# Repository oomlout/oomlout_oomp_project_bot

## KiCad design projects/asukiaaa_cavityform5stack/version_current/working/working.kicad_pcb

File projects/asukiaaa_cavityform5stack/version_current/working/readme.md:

# OOMP Project  
## CavityForM5Stack  by asukiaaa  
  
oomp key: oomp_projects_flat_asukiaaa_cavityform5stack  
(snippet of original readme)  
  
- CavityForM5Stack  
  
PCBs to create a cavity for M5Stack.  

- License  
  
MIT  
  
- References  
  
- [CavityForM5Stack ピンソケット、ブレッドボード無し](https://www.switch-science.com/catalog/5684/)  
- [CavityForM5Stack ピンソケット、ブレッドボード付き](https://www.switch-science.com/catalog/5685/)  
- [M5StackのStackに背の高い部品を利用できるM5StackCavityを作ってみた](http://asukiaaa.blogspot.com/2019/08/m5stackstackm5stackcavity.html)  
  
  full source readme at [readme_src.md](readme_src.md)  
  
source repo at: [https://github.com/asukiaaa/CavityForM5Stack](https://github.com/asukiaaa/CavityForM5Stack)  
## Board  

## Schematic  

[schematic pdf](working_schematic.pdf)  
## Images

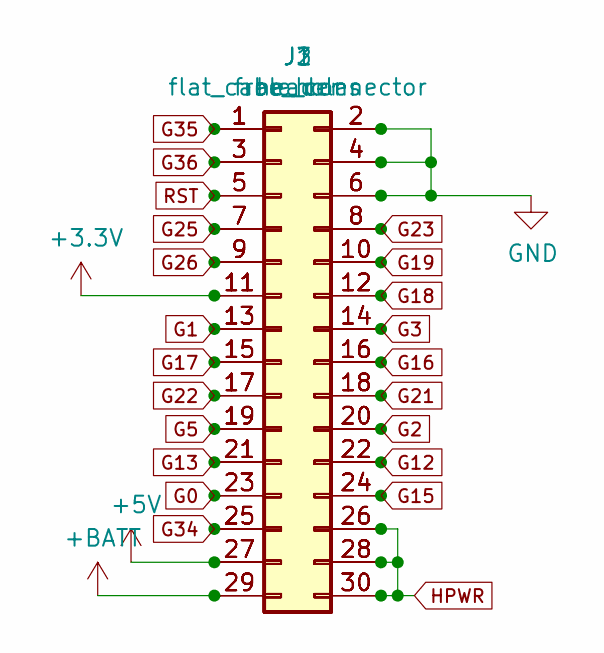
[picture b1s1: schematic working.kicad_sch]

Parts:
J1: flat_cable_connector; Hirose_FH12-30S-0.5SH_1x30-1MP_P0.50mm_Horizontal
J2: header; PinHeader_2x15_P2.54mm_Vertical_SMD_for_M5Stack
J3: free_holes; PinHeader_1x30_P1.27mm_Vertical_without_silks

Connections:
+3V3: J1.11, J2.11, J3.11
+5V: J1.27, J2.27, J3.27
+BATT: J1.29, J2.29, J3.29
G0: J1.23, J2.23, J3.23
G1: J1.13, J2.13, J3.13
G2: J1.20, J2.20, J3.20
G3: J1.14, J2.14, J3.14
G5: J1.19, J2.19, J3.19
G12: J1.22, J2.22, J3.22
G13: J1.21, J2.21, J3.21
G15: J1.24, J2.24, J3.24
G16: J1.16, J2.16, J3.16
G17: J1.15, J2.15, J3.15
G18: J1.12, J2.12, J3.12
G19: J1.10, J2.10, J3.10
G21: J1.18, J2.18, J3.18
G22: J1.17, J2.17, J3.17
G23: J1.8, J2.8, J3.8
G25: J1.7, J2.7, J3.7
G26: J1.9, J2.9, J3.9
G34: J1.25, J2.25, J3.25
G35: J1.1, J2.1, J3.1
G36: J1.3, J2.3, J3.3
GND: J1.2, J1.4, J1.6, J2.2, J2.4, J2.6, J3.2, J3.4, J3.6
HPWR: J1.26, J1.28, J1.30, J2.26, J2.28, J2.30, J3.26, J3.28, J3.30
RST: J1.5, J2.5, J3.5

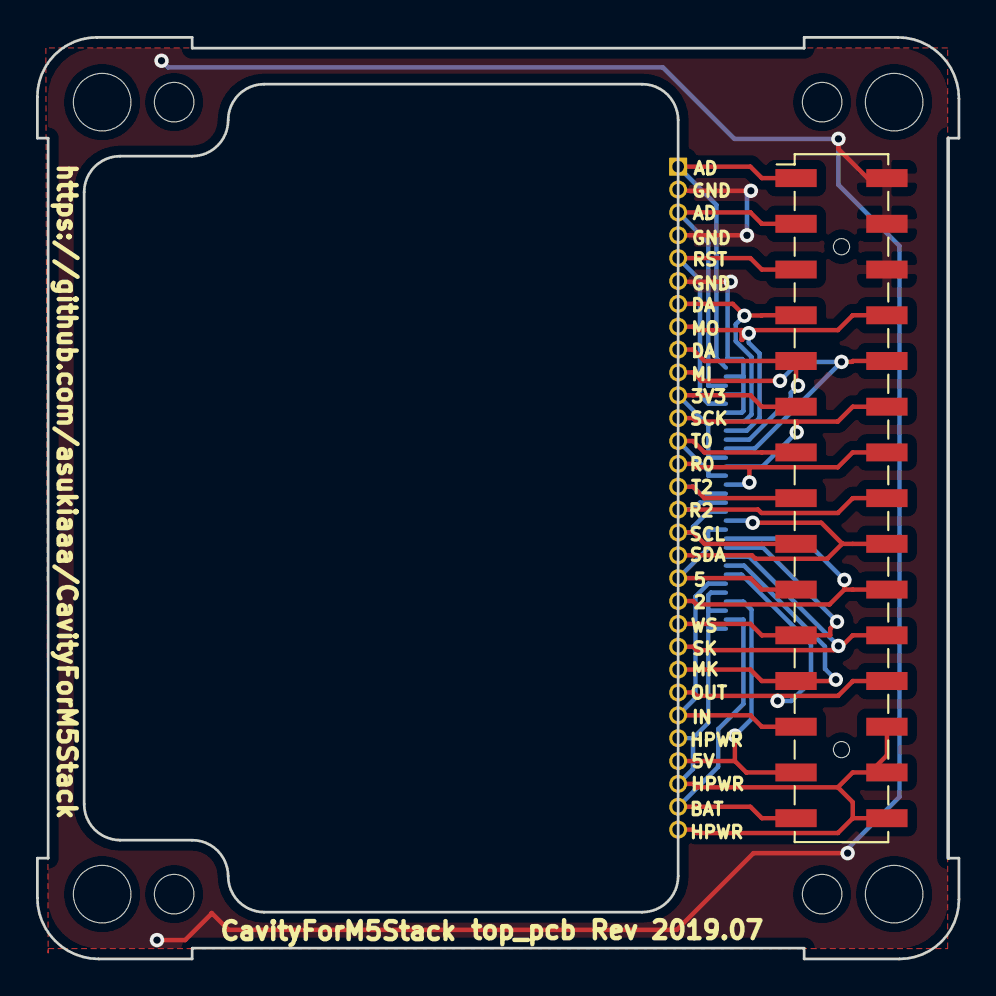
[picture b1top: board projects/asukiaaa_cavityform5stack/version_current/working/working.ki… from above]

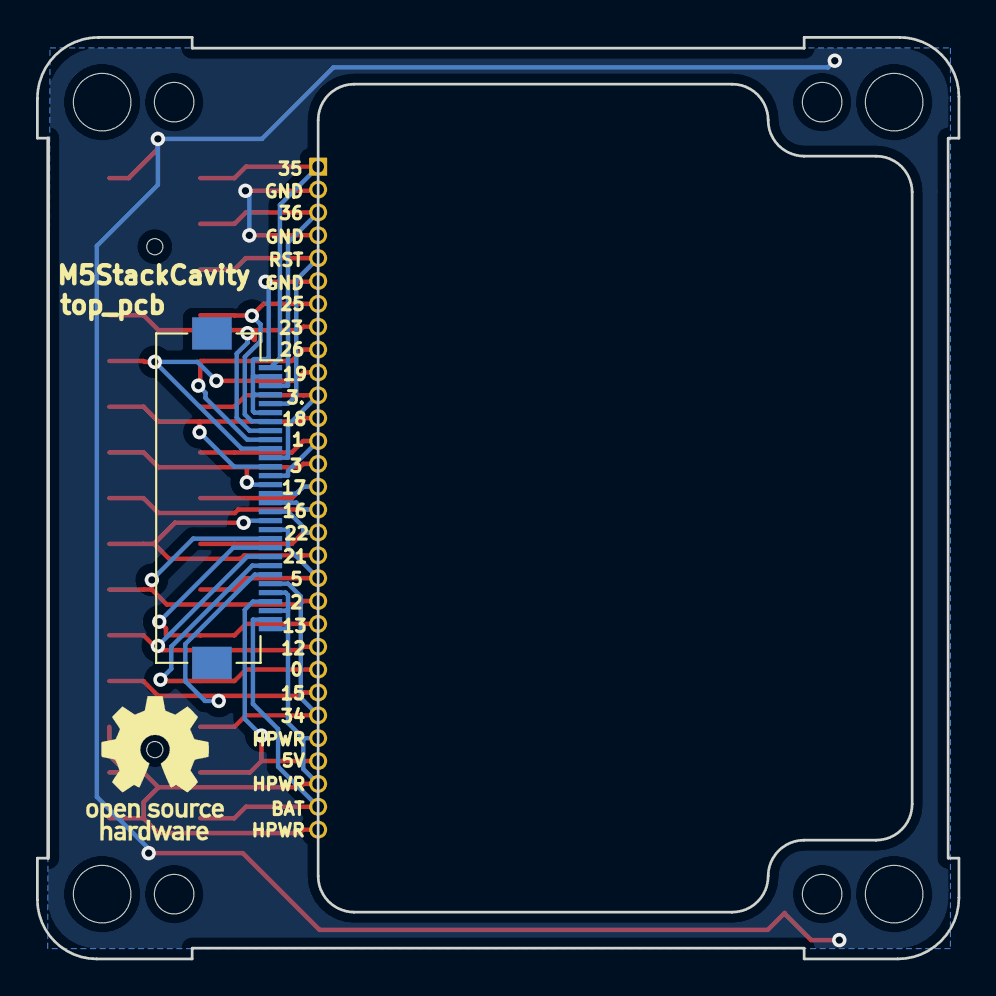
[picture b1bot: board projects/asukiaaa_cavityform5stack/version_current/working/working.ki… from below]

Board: 2 copper layers, 51.2 x 51.2 mm, 16 parts (2 on the bottom side), 26 nets.

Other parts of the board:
OSHWREF2: OSHW-Logo_7.5x8mm_SilkScreen
REF1, REF4, REF6, REF9: MountingHole_3.2mm_M3
REF2, REF3, REF7, REF8: MountingHole_2.2mm_M2
corner1, corner4: corner_edge1
corner2, corner3: corner_edge2

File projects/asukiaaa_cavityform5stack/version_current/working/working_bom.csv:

"Id";"Designator";"Footprint";"Quantity";"Designation";"Supplier and ref";
1;"J2";"PinHeader_2x15_P2.54mm_Vertical_SMD_for_M5Stack";1;"header";;;
2;"corner4,corner1";"corner_edge1";2;"corner_edge1";;;
3;"corner3,corner2";"corner_edge2";2;"corner_edge2";;;
4;"J1";"Hirose_FH12-30S-0.5SH_1x30-1MP_P0.50mm_Horizontal";1;"flat_cable_connector";;;
5;"J3";"PinHeader_1x30_P1.27mm_Vertical_without_silks";1;"free_holes";;;

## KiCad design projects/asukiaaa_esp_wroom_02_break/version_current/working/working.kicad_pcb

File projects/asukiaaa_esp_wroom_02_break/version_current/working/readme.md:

# esp-wroom-02-break by asukiaaa  
This is a harvested standardized copy of a project from github.  
The original project can be found at:  
https://github.com/asukiaaa/esp-wroom-02-break  
Please consult that link for additional, details, files, and license information.  
Note: It was auto harvested and if the original repo had more than one board file or anything out of the ordinary the files here are likely not representative.

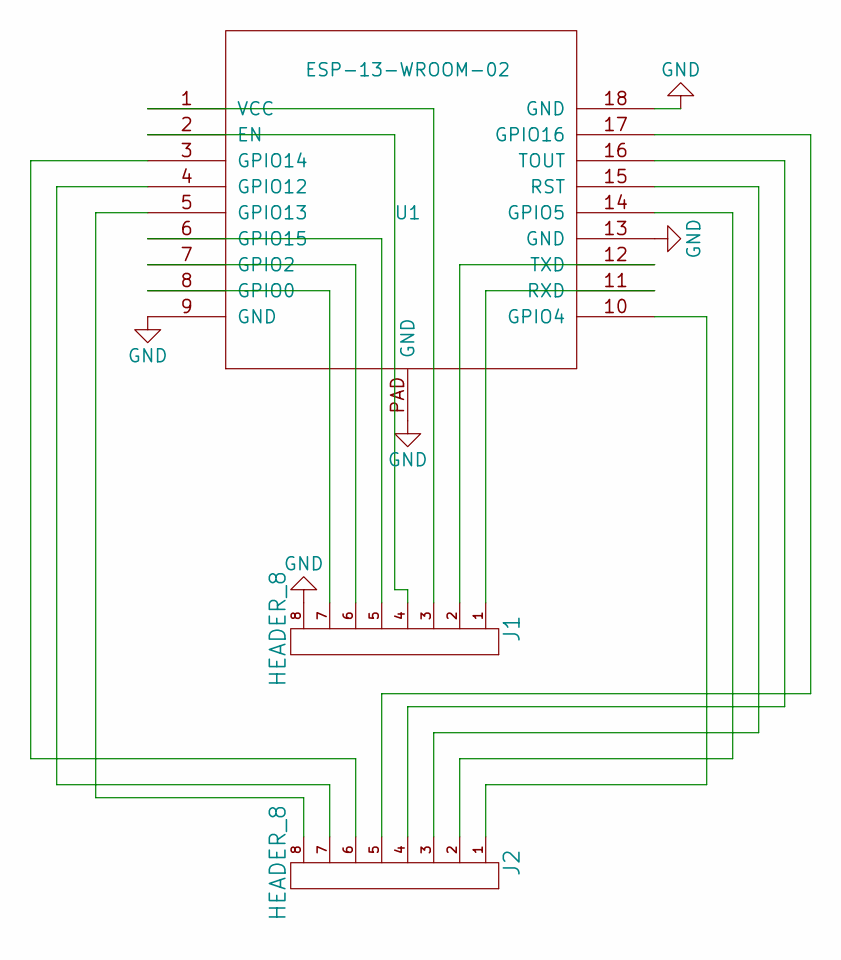
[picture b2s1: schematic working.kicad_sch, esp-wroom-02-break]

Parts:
J1, J2: HEADER_8; Pin_Header_Straight_1x08_small
U1: ESP-13-WROOM-02

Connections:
GND: J1.8, U1.9 (GND), U1.13 (GND), U1.18 (GND), U1.PAD (GND)
unnamed: J1.1, U1.11 (RXD)
unnamed: J1.2, U1.12 (TXD)
unnamed: J1.3, U1.1 (VCC)
unnamed: J1.4, U1.2 (EN)
unnamed: J1.5, U1.6 (GPIO15)
unnamed: J1.6, U1.7 (GPIO2)
unnamed: J1.7, U1.8 (GPIO0)
unnamed: J2.1, U1.10 (GPIO4)
unnamed: J2.2, U1.14 (GPIO5)
unnamed: J2.3, U1.15 (RST)
unnamed: J2.4, U1.16 (TOUT)
unnamed: J2.5, U1.17 (GPIO16)
unnamed: J2.6, U1.3 (GPIO14)
unnamed: J2.7, U1.4 (GPIO12)
unnamed: J2.8, U1.5 (GPIO13)

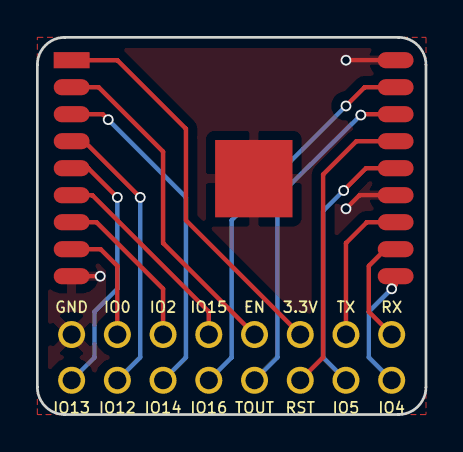
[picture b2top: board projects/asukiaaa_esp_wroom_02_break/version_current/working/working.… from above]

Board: 2 copper layers, 21.6 x 21.0 mm, 3 parts (0 on the bottom side), 16 nets.

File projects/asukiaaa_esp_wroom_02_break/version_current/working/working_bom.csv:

"Id";"Designator";"Footprint";"Quantity";"Designation";"Supplier and ref";
1;"U1";"ESP-13-WROOM-02";1;"ESP-13-WROOM-02";;;
2;"J1,J2";"Pin_Header_Straight_1x08_small";2;"HEADER_8";;;
3;"G***";"oshw-3p4mm";1;"LOGO";;;

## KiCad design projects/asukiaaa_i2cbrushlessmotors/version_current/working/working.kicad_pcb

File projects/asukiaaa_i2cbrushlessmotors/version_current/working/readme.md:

# I2cBrushlessMotors by asukiaaa  
This is a harvested standardized copy of a project from github.  
The original project can be found at:  
https://github.com/asukiaaa/I2cBrushlessMotors  
Please consult that link for additional, details, files, and license information.  
Note: It was auto harvested and if the original repo had more than one board file or anything out of the ordinary the files here are likely not representative.

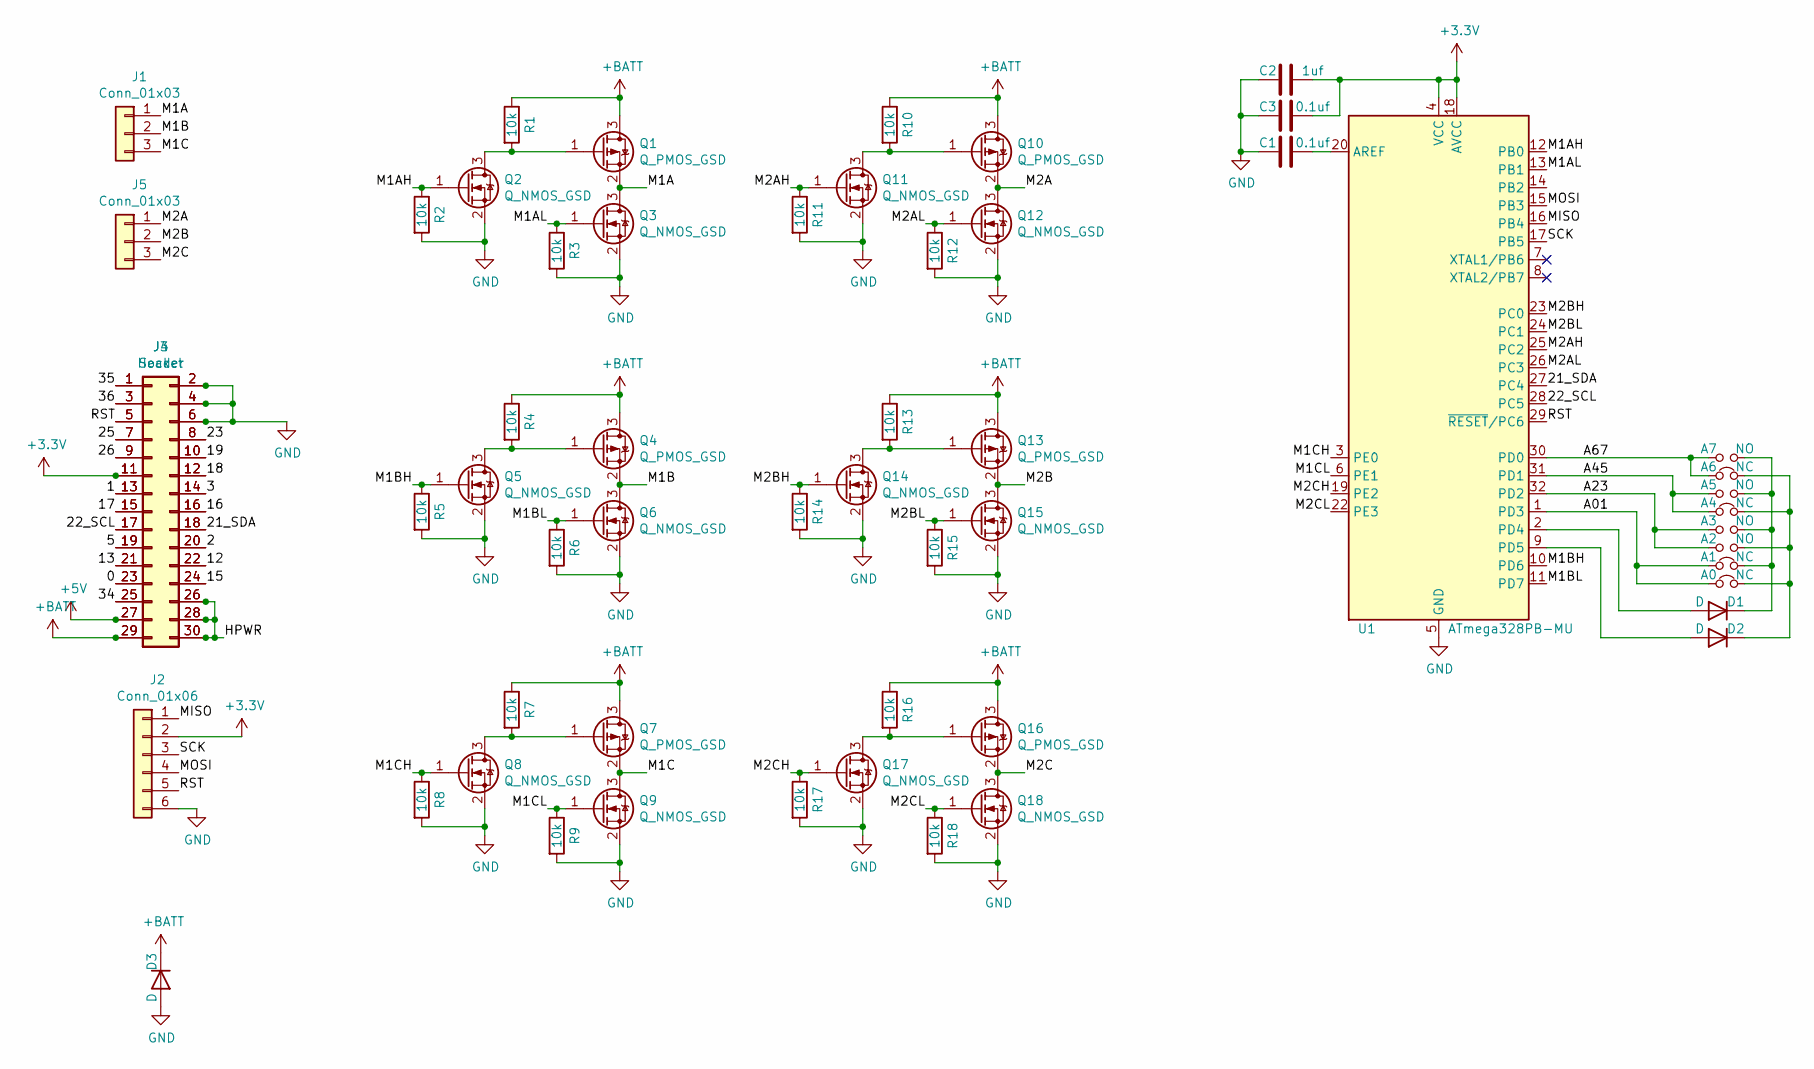
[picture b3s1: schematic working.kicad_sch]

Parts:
A0, A1, A4, A6: NC; SolderJumper-2_P1.3mm_Bridged_RoundedPad1.0x1.5mm
A2, A3, A5, A7: NO; SolderJumper-2_P1.3mm_Open_RoundedPad1.0x1.5mm
C1, C3: 0.1uf; C_0603_1608Metric
C2: 1uf; C_0603_1608Metric
D1, D2: D; D_SOD-323
D3: D; D_SOD-123F
J1, J5: Conn_01x03; Molex_1x03_P1.25mm_Vertical
J2: Conn_01x06; 2x03_P2.54mm_Pads
J3: Header; PinHeader_2x15_P2.54mm_M5Stack
J4: Socket; PinSocket_2x15_P2.54mm_Vertical_SMD_just_for_M5Stack_bottom
Q1, Q4, Q7, Q10, Q13, Q16: Q_PMOS_GSD; SOT-23
Q2, Q3, Q5, Q6, Q8, Q9, Q11, Q12, Q14, Q15, Q17, Q18: Q_NMOS_GSD; SOT-23
R1, R2, R3, R4, R5, R6, R7, R8, R9, R10, R11, R12, R13, R14, R15, R16, R17, R18: 10k; R_0603_1608Metric
U1: ATmega328PB-MU; QFN-32-1EP_5x5mm_P0.5mm_EP3.1x3.1mm

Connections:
+3V3: C2.2, C3.2, J2.2, J3.11, J4.11, U1.4 (VCC), U1.18 (AVCC)
+5V: J3.27, J4.27
+BATT: D3.1 (K), J3.29, J4.29, Q1.3 (D), Q4.3 (D), Q7.3 (D), Q10.3 (D), Q13.3 (D), Q16.3 (D), R1.1, R4.1, R7.1, R10.1, R13.1, R16.1
/0: J3.23, J4.23
/1: J3.13, J4.13
/2: J3.20, J4.20
/3: J3.14, J4.14
/5: J3.19, J4.19
/12: J3.22, J4.22
/13: J3.21, J4.21
/15: J3.24, J4.24
/16: J3.16, J4.16
/17: J3.15, J4.15
/18: J3.12, J4.12
/19: J3.10, J4.10
/21_SDA: J3.18, J4.18, U1.27 (PC4)
/22_SCL: J3.17, J4.17, U1.28 (PC5)
/23: J3.8, J4.8
/25: J3.7, J4.7
/26: J3.9, J4.9
/34: J3.25, J4.25
/35: J3.1, J4.1
/36: J3.3, J4.3
/A01: A0.1, A1.1, U1.1 (PD3)
/A23: A2.1, A3.1, U1.32 (PD2)
/A45: A4.1, A5.1, U1.31 (PD1)
/A67: A6.1, A7.1, U1.30 (PD0)
/HPWR: J3.26, J3.28, J3.30, J4.26, J4.28, J4.30
/M1A: J1.1, Q1.2 (S), Q3.3 (D)
/M1AH: Q2.1 (G), R2.1, U1.12 (PB0)
/M1AL: Q3.1 (G), R3.1, U1.13 (PB1)
/M1B: J1.2, Q4.2 (S), Q6.3 (D)
/M1BH: Q5.1 (G), R5.1, U1.10 (PD6)
/M1BL: Q6.1 (G), R6.1, U1.11 (PD7)
/M1C: J1.3, Q7.2 (S), Q9.3 (D)
/M1CH: Q8.1 (G), R8.1, U1.3 (PE0)
/M1CL: Q9.1 (G), R9.1, U1.6 (PE1)
/M2A: J5.1, Q10.2 (S), Q12.3 (D)
/M2AH: Q11.1 (G), R11.1, U1.25 (PC2)
/M2AL: Q12.1 (G), R12.1, U1.26 (PC3)
/M2B: J5.2, Q13.2 (S), Q15.3 (D)
/M2BH: Q14.1 (G), R14.1, U1.23 (PC0)
/M2BL: Q15.1 (G), R15.1, U1.24 (PC1)
/M2C: J5.3, Q16.2 (S), Q18.3 (D)
/M2CH: Q17.1 (G), R17.1, U1.19 (PE2)
/M2CL: Q18.1 (G), R18.1, U1.22 (PE3)
/MISO: J2.1, U1.16 (PB4)
/MOSI: J2.4, U1.15 (PB3)
/RST: J2.5, J3.5, J4.5, U1.29 (~RESET/PC6)
/SCK: J2.3, U1.17 (PB5)
GND: C1.1, C2.1, C3.1, D3.2 (A), J2.6, J3.2, J3.4, J3.6, J4.2, J4.4, J4.6, Q2.2 (S), Q3.2 (S), Q5.2 (S), Q6.2 (S), Q8.2 (S), Q9.2 (S), Q11.2 (S), Q12.2 (S), Q14.2 (S), Q15.2 (S), Q17.2 (S), Q18.2 (S), R2.2, R3.2, R5.2, R6.2, R8.2, R9.2, R11.2, R12.2, R14.2, R15.2, R17.2, R18.2, U1.5 (GND), U1.21 (GND), U1.33 (GND)
unnamed: A0.2, A2.2, A4.2, A6.2, D2.1 (K)
unnamed: A1.2, A3.2, A5.2, A7.2, D1.1 (K)
unnamed: C1.2, U1.20 (AREF)
unnamed: D1.2 (A), U1.2 (PD4)
unnamed: D2.2 (A), U1.9 (PD5)
unnamed: Q1.1 (G), Q2.3 (D), R1.2
unnamed: Q4.1 (G), Q5.3 (D), R4.2
unnamed: Q7.1 (G), Q8.3 (D), R7.2
unnamed: Q10.1 (G), Q11.3 (D), R10.2
unnamed: Q13.1 (G), Q14.3 (D), R13.2
unnamed: Q16.1 (G), Q17.3 (D), R16.2

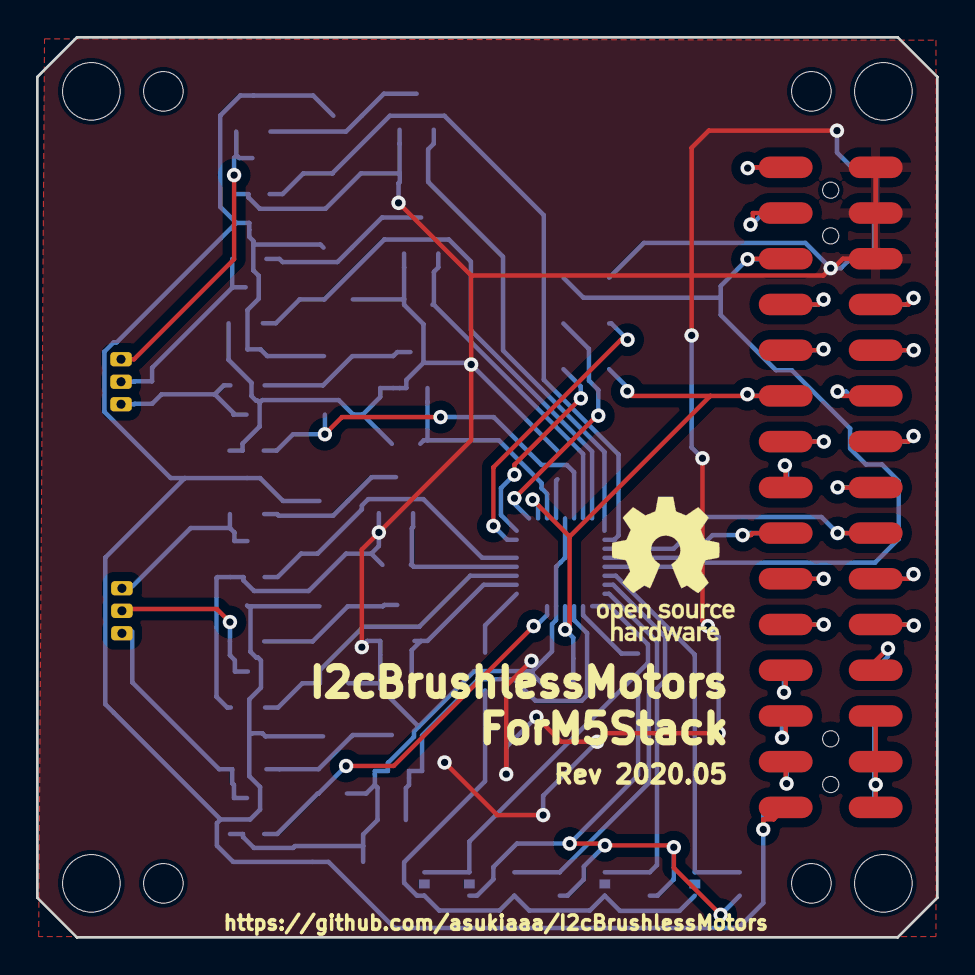
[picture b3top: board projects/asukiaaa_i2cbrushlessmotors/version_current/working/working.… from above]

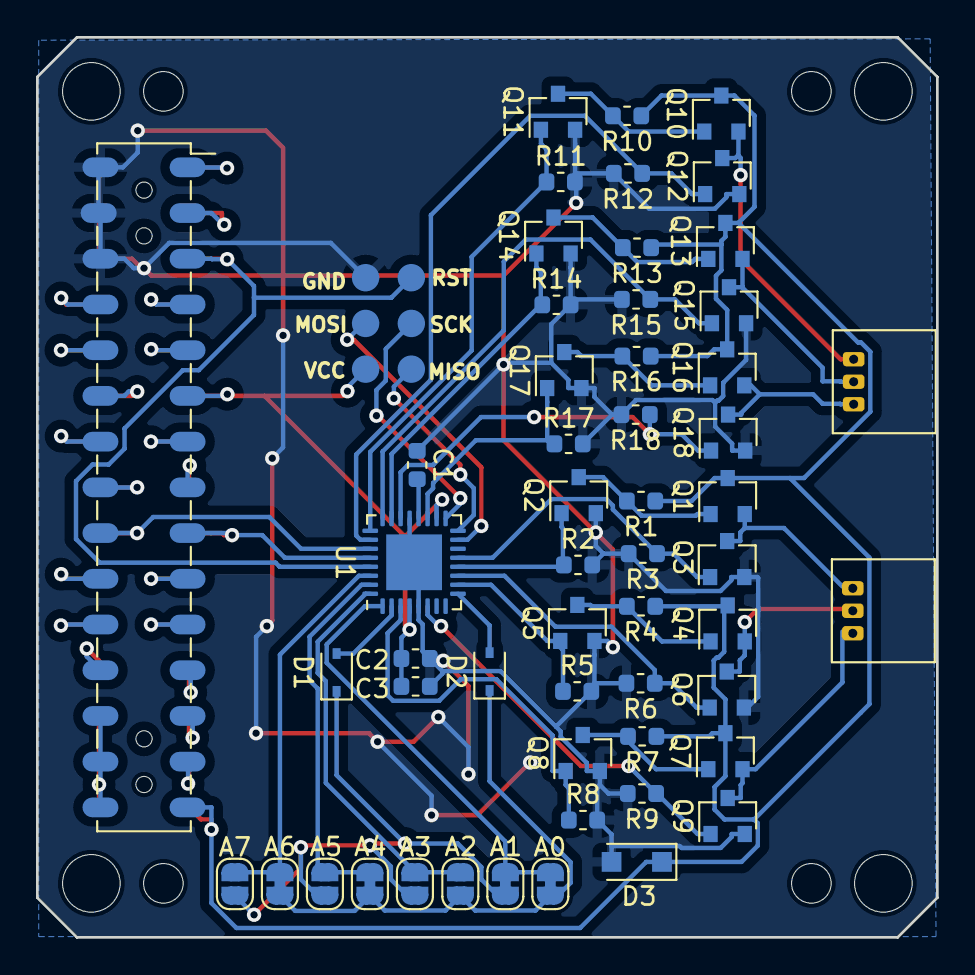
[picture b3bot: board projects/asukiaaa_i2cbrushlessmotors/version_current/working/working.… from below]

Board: 2 copper layers, 50.0 x 50.0 mm, 64 parts (55 on the bottom side), 62 nets.

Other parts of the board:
REF1, REF4, REF6, REF9: MountingHole_3.2mm_M3
REF2, REF3, REF7, REF8: MountingHole_2.2mm_M2

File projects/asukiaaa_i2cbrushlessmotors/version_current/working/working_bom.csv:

"Id";"Designator";"Footprint";"Quantity";"Designation";"Supplier and ref";
1;"J5,J1";"Molex_1x03_P1.25mm_Vertical";2;"Conn_01x03";;;
2;"D2,D1";"D_SOD-323";2;"D";;;
3;"D3";"D_SOD-123F";1;"D";;;
4;"C3,C1";"C_0603_1608Metric";2;"0.1uf";;;
5;"C2";"C_0603_1608Metric";1;"1uf";;;
6;"R9,R8,R2,R1,R4,R10,R12,R15,R5,R7,R16,R14,R11,R18,R6,R13,R17,R3";"R_0603_1608Metric";18;"10k";;;
7;"Q7,Q1,Q4,Q10,Q13,Q16";"SOT-23";6;"Q_PMOS_GSD";;;
8;"Q15,Q18,Q6,Q14,Q9,Q5,Q12,Q8,Q3,Q17,Q11,Q2";"SOT-23";12;"Q_NMOS_GSD";;;
9;"U1";"QFN-32-1EP_5x5mm_P0.5mm_EP3.1x3.1mm";1;"ATmega328PB-MU";;;
10;"J3";"PinHeader_2x15_P2.54mm_M5Stack";1;"Header";;;
11;"J2";"2x03_P2.54mm_Pads";1;"Conn_01x06";;;
12;"J4";"PinSocket_2x15_P2.54mm_Vertical_SMD_just_for_M5Stack_bottom";1;"Socket";;;

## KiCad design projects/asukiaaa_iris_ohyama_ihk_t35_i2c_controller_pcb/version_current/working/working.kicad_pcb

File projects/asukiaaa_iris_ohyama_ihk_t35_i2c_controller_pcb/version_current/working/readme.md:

# IRIS-OHYAMA-IHK-T35-I2C-Controller-PCB by asukiaaa  
This is a harvested standardized copy of a project from github.  
The original project can be found at:  
https://github.com/asukiaaa/IRIS-OHYAMA-IHK-T35-I2C-Controller-PCB  
Please consult that link for additional, details, files, and license information.  
Note: It was auto harvested and if the original repo had more than one board file or anything out of the ordinary the files here are likely not representative.

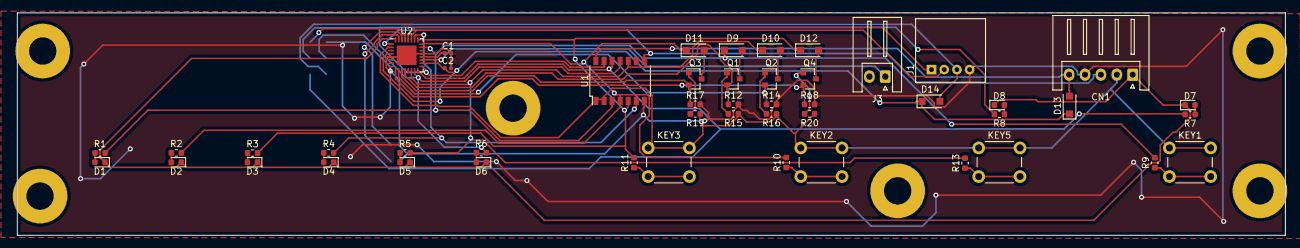
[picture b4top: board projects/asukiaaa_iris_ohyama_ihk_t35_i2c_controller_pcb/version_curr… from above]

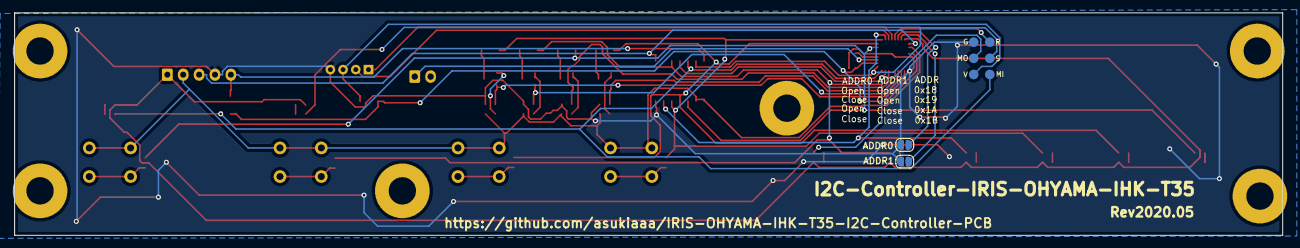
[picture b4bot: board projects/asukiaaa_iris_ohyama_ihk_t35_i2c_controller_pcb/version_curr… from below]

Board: 2 copper layers, 199.5 x 35.0 mm, 58 parts (3 on the bottom side), 46 nets.

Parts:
C1, C2: 0.1uf; C_0402_1005Metric
CN1: Conn_01x05; JST_XH_S5B-XH-A_1x05_P2.50mm_Horizontal
D1: Level1; LED_0603_1608Metric
D2: Level2; LED_0603_1608Metric
D3: Level3; LED_0603_1608Metric
D4: Level4; LED_0603_1608Metric
D5: Level5; LED_0603_1608Metric
D6: Level6; LED_0603_1608Metric
D7: NomalState; LED_0603_1608Metric
D8: OilState; LED_0603_1608Metric
D9, D10, D11, D12, D13, D14: D; D_SOD-123F
J1: Grove; NS-Tech_Grove_1x04_P2mm_Horizontal
J2: Conn_01x06; 2x03_P2.54mm_Pads
J3: thermistor; JST_XH_S2B-XH-A_1x02_P2.50mm_Horizontal
JP1: ADDR0_NO; SolderJumper-2_P1.3mm_Open_RoundedPad1.0x1.5mm
JP2: ADDR1_NO; SolderJumper-2_P1.3mm_Open_RoundedPad1.0x1.5mm
KEY1: normal_power; SW_PUSH_6mm_center_like_smd
KEY2: power_up; SW_PUSH_6mm_center_like_smd
KEY3: power_down; SW_PUSH_6mm_center_like_smd
KEY5: oil_power; SW_PUSH_6mm_center_like_smd
Q1, Q2, Q3, Q4: Q_NMOS_DGS; SOT-23
R1, R2, R3, R4, R5, R6, R7, R8, R12, R14, R15, R16, R17, R18, R19, R20: 1k; R_0603_1608Metric
R9, R10, R11, R13: 2k; R_0603_1608Metric
REF1, REF2, REF3, REF4, REF5, REF6: MountingHole_4.3mm_M4_Pad
U1: 74HC164; SOP-14_4.4x9.2mm_P1.27mm
U2: ATmega328P-MU; QFN-32-1EP_5x5mm_P0.5mm_EP3.1x3.1mm

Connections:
+5V: CN1.5, D13.2, U1.14
/A0: D9.1, R1.2, R9.2, U1.3, U2.23
/A1: D11.1, R2.2, R10.2, U1.4, U2.24
/A2: D12.1, R3.2, R11.2, U1.5, U2.25
/A3: R4.2, U1.6, U2.26
/A6: J3.1, U2.19
/ADDR0: JP1.1, U2.30
/ADDR1: JP2.1, U2.31
/CLK: CN1.3, U1.8, U2.1
/Controller_5V: C2.1, D13.1, D14.1, U2.4, U2.18
/D2: CN1.1, D1.1, D2.1, D3.1, D4.1, D5.1, D6.1, D7.1, D8.1, U2.32
/D4: CN1.2, KEY1.1, KEY2.1, KEY3.1, KEY5.1, R15.1, R16.1, R19.1, R20.1, U1.1, U1.2, U2.2
/D5: Q4.2, R18.1, U2.9
/D6: Q2.2, R14.1, U2.10
/D7: Q3.2, R17.1, U2.11
/D8: Q1.2, R12.1, U2.12
/D10: D10.1, R5.2, R13.2, U1.10, U2.14
/D11: J2.4, R6.2, U1.11, U2.15
/D12: J2.1, R7.2, U1.12, U2.16
/D13: J2.3, R8.2, U1.13, U2.17
/GROVE_5V: D14.2, J1.3, J2.2
/RST: J2.5, U2.29
/SCL: J1.1, U2.28
/SDA: J1.2, U2.27
GND: C1.2, C2.2, CN1.4, J1.4, J2.6, JP1.2, JP2.2, R12.2, R14.2, R17.2, R18.2, U1.7, U2.5, U2.21, U2.33
unnamed: C1.1, U2.20
unnamed: D1.2, R1.1
unnamed: D2.2, R2.1
unnamed: D3.2, R3.1
unnamed: D4.2, R4.1
unnamed: D5.2, R5.1
unnamed: D6.2, R6.1
unnamed: D7.2, R7.1
unnamed: D8.2, R8.1
unnamed: D9.2, Q1.3
unnamed: D10.2, Q2.3
unnamed: D11.2, Q3.3
unnamed: D12.2, Q4.3
unnamed: KEY1.2, R9.1
unnamed: KEY2.2, R10.1
unnamed: KEY3.2, R11.1
unnamed: KEY5.2, R13.1
unnamed: Q1.1, R15.2
unnamed: Q2.1, R16.2
unnamed: Q3.1, R19.2
unnamed: Q4.1, R20.2

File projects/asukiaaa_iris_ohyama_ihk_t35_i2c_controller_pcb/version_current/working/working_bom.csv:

"Id";"Designator";"Footprint";"Quantity";"Designation";"Supplier and ref";
1;"KEY5";"SW_PUSH_6mm_center_like_smd";1;"oil_power";;;
2;"KEY3";"SW_PUSH_6mm_center_like_smd";1;"power_down";;;
3;"KEY2";"SW_PUSH_6mm_center_like_smd";1;"power_up";;;
4;"KEY1";"SW_PUSH_6mm_center_like_smd";1;"normal_power";;;
5;"CN1";"JST_XH_S5B-XH-A_1x05_P2.50mm_Horizontal";1;"Conn_01x05";;;
6;"J3";"JST_XH_S2B-XH-A_1x02_P2.50mm_Horizontal";1;"thermistor";;;
7;"U2";"QFN-32-1EP_5x5mm_P0.5mm_EP3.1x3.1mm";1;"ATmega328P-MU";;;
8;"U1";"SOP-14_4.4x9.2mm_P1.27mm";1;"74HC164";;;
9;"R20,R19,R18,R17,R16,R15,R14,R12,R8,R7,R6,R5,R4,R3,R2,R1";"R_0603_1608Metric";16;"1k";;;
10;"R13,R11,R10,R9";"R_0603_1608Metric";4;"2k";;;
11;"Q4,Q3,Q2,Q1";"SOT-23";4;"Q_NMOS_DGS";;;
12;"J2";"2x03_P2.54mm_Pads";1;"Conn_01x06";;;
13;"J1";"NS-Tech_Grove_1x04_P2mm_Horizontal";1;"Grove";;;
14;"D14,D13,D12,D11,D10,D9";"D_SOD-123F";6;"D";;;
15;"D8";"LED_0603_1608Metric";1;"OilState";;;
16;"D7";"LED_0603_1608Metric";1;"NomalState";;;
17;"D6";"LED_0603_1608Metric";1;"Level6";;;
18;"D5";"LED_0603_1608Metric";1;"Level5";;;
19;"D4";"LED_0603_1608Metric";1;"Level4";;;
20;"D3";"LED_0603_1608Metric";1;"Level3";;;
21;"D2";"LED_0603_1608Metric";1;"Level2";;;
22;"D1";"LED_0603_1608Metric";1;"Level1";;;
23;"C2,C1";"C_0402_1005Metric";2;"0.1uf";;;

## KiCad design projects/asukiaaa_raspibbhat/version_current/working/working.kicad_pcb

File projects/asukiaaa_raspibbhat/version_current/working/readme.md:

# RaspiBBHat by asukiaaa  
This is a harvested standardized copy of a project from github.  
The original project can be found at:  
https://github.com/asukiaaa/RaspiBBHat  
Please consult that link for additional, details, files, and license information.  
Note: It was auto harvested and if the original repo had more than one board file or anything out of the ordinary the files here are likely not representative.

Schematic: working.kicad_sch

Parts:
J1, J3: Conn_01x03; PinSocket_1x03_P2.54mm_Vertical
J2, J4: Conn_01x16; PinSocket_1x16_P2.54mm_Vertical
J5: Raspberry_Pi_2_3; PinHeader_2x20_P2.54mm_Vertical

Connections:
+3V3: J2.1, J2.9, J5.1, J5.17
+5C: J4.1, J4.2, J5.2, J5.4
GND: J2.5, J2.13, J4.3, J4.7, J4.10, J4.15, J5.6, J5.9, J5.14, J5.20, J5.25, J5.30, J5.34, J5.39
GPIO2(SDA1): J2.2, J5.3
GPIO3(SCL1): J2.3, J5.5
GPIO4(GCLK): J2.4, J5.7
GPIO5: J2.15, J5.29
GPIO6: J2.16, J5.31
GPIO7(SPI_CE1): J4.13, J5.26
GPIO8(SPI_CE0): J4.12, J5.24
GPIO9(SPI_MISO): J2.11, J5.21
GPIO10(SPI_MOSI): J2.10, J5.19
GPIO11(SPI_SCLK): J2.12, J5.23
GPIO12: J4.16, J5.32
GPIO13: J1.1, J5.33
GPIO14(TXD): J4.4, J5.8
GPIO15(RXD): J4.5, J5.10
GPIO16: J3.1, J5.36
GPIO17(GEN0): J2.6, J5.11
GPIO18(GEN1): J4.6, J5.12
GPIO19: J1.2, J5.35
GPIO20: J3.2, J5.38
GPIO21: J3.3, J5.40
GPIO22(GEN3): J2.8, J5.15
GPIO23(GEN4): J4.8, J5.16
GPIO24(GEN5): J4.9, J5.18
GPIO25(GEN6): J4.11, J5.22
GPIO26: J1.3, J5.37
GPIO27(GEN2): J2.7, J5.13
ID_SC: J4.14, J5.28
ID_SD: J2.14, J5.27

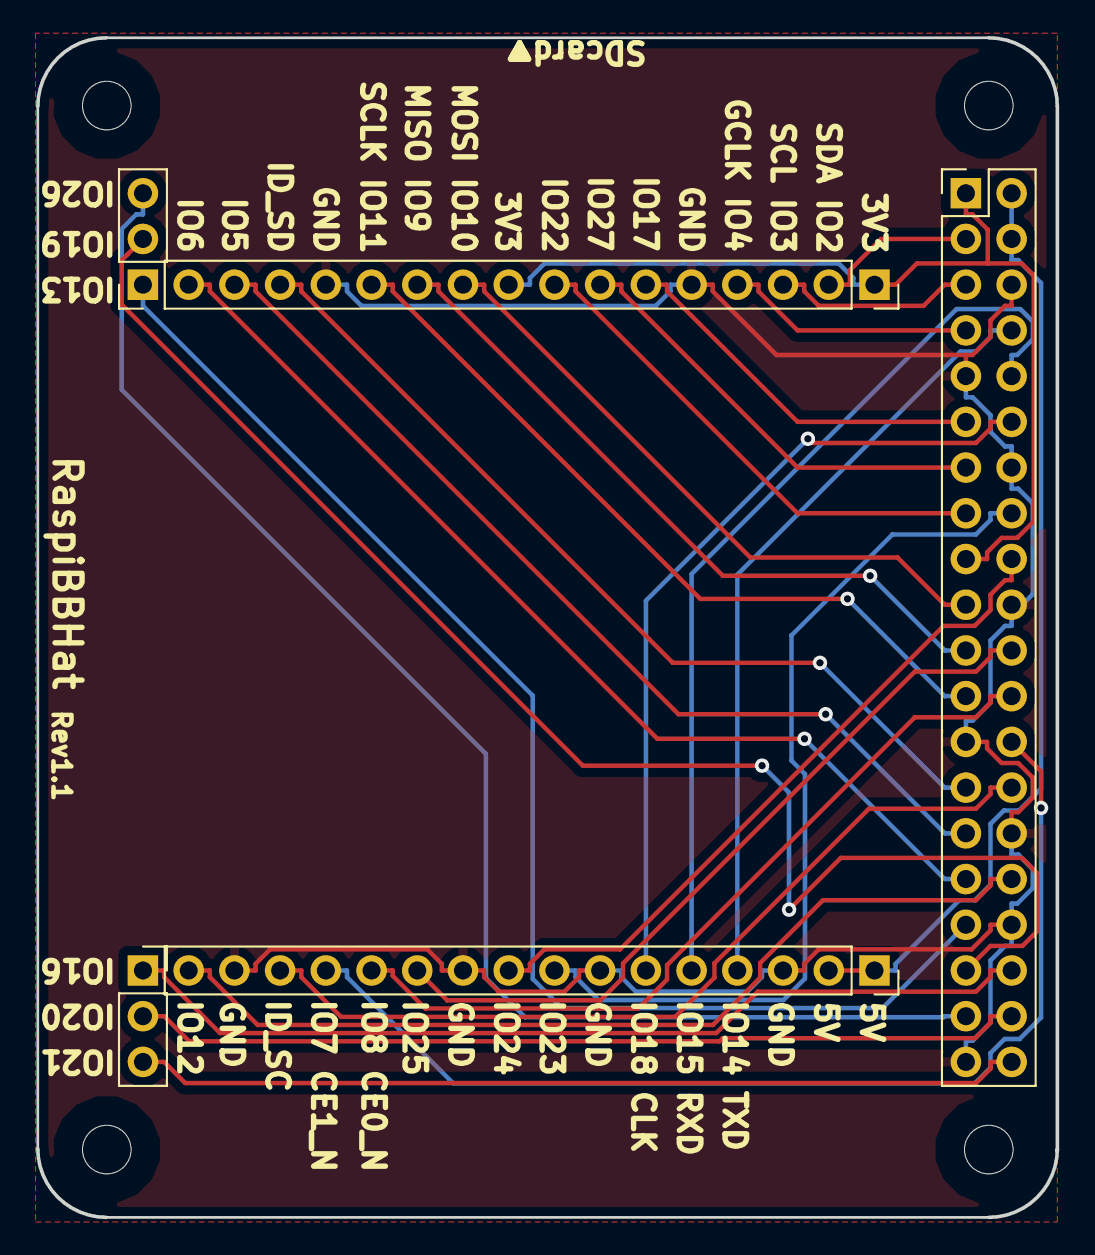
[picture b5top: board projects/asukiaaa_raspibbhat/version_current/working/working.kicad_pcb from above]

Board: 2 copper layers, 56.6 x 65.5 mm, 9 parts (0 on the bottom side), 31 nets.

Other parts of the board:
REF1, REF2, REF3, REF4: MountingHole_2.7mm; LargeClearanceMountingHole_2.7mm

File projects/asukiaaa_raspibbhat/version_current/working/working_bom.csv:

"Id";"Designator";"Footprint";"Quantity";"Designation";"Supplier and ref";
1;"J1,J3";"PinSocket_1x03_P2.54mm_Vertical";2;"Conn_01x03";;;
2;"J5";"PinHeader_2x20_P2.54mm_Vertical";1;"Raspberry_Pi_2_3";;;
3;"J2,J4";"PinSocket_1x16_P2.54mm_Vertical";2;"Conn_01x16";;;

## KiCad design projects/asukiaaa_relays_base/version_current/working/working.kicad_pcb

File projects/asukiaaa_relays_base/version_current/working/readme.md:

# relays_base by asukiaaa  
This is a harvested standardized copy of a project from github.  
The original project can be found at:  
https://github.com/asukiaaa/relays_base  
Please consult that link for additional, details, files, and license information.  
Note: It was auto harvested and if the original repo had more than one board file or anything out of the ordinary the files here are likely not representative.

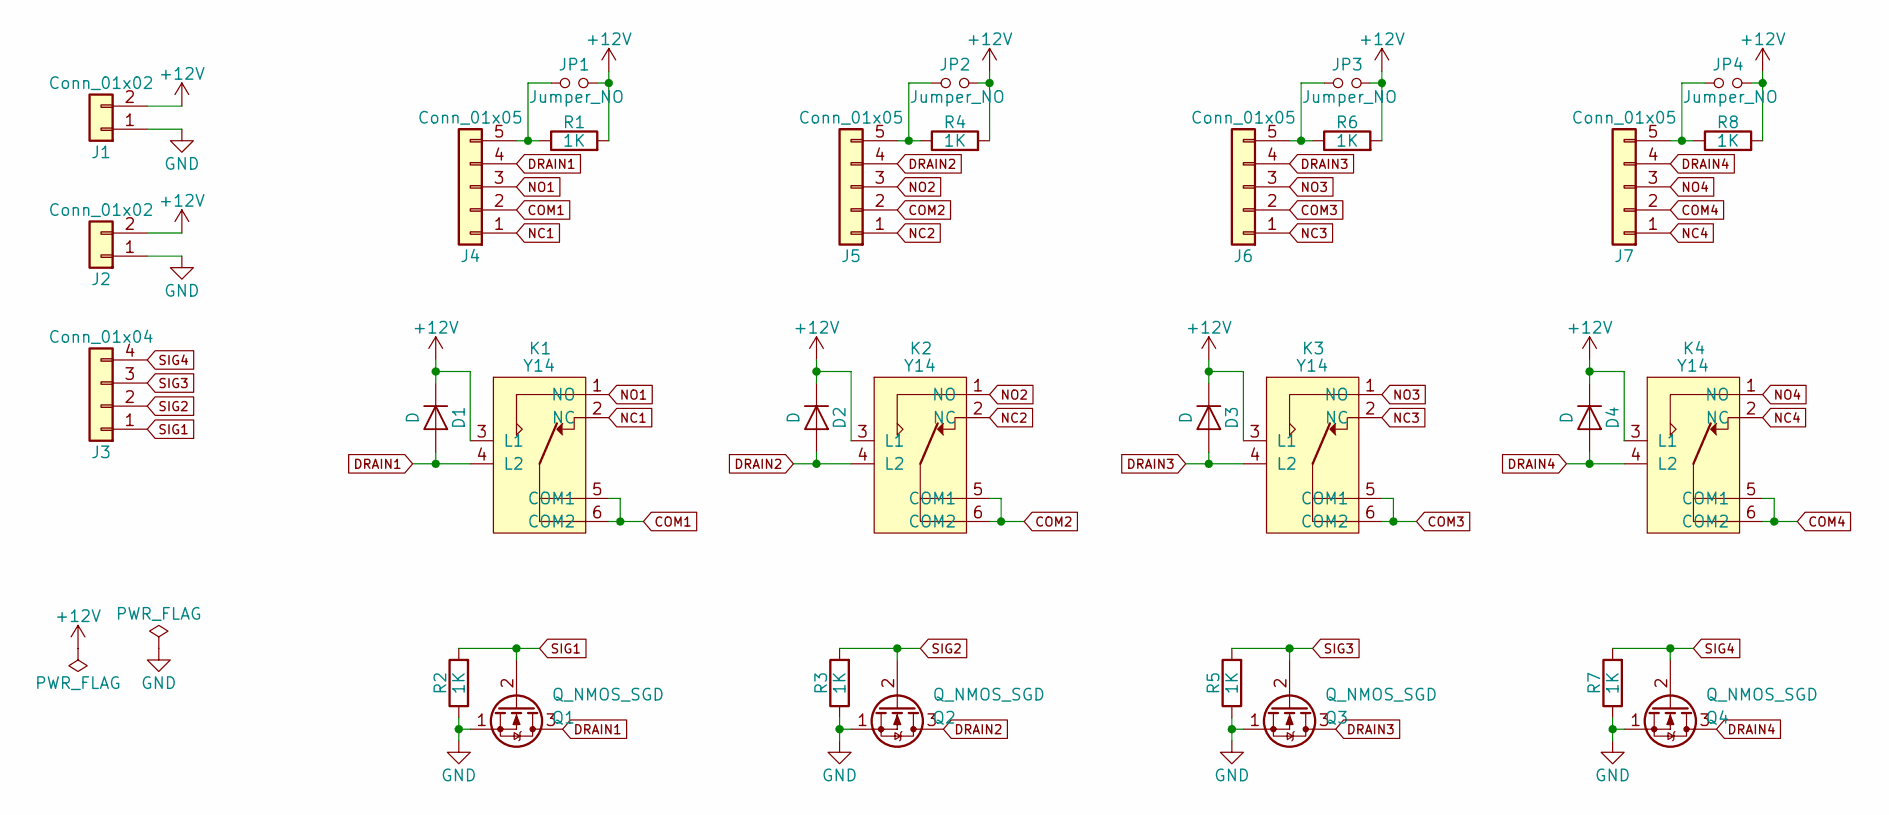
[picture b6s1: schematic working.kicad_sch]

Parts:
D1, D2, D3, D4: D; D_A-405_P7.62mm_Horizontal
J1, J2: Conn_01x02; PinHeader_1x02_P2.54mm_Vertical
J3: Conn_01x04; PinHeader_1x04_P2.54mm_Vertical
J4, J5, J6, J7: Conn_01x05; PinHeader_1x05_P2.54mm_Vertical
JP1, JP2, JP3, JP4: Jumper_NO; SolderJumper_01x02
K1, K2, K3, K4: Y14; Relay_Y14
Q1, Q2, Q3, Q4: Q_NMOS_SGD; TO-92_Inline
R1, R2, R3, R4, R5, R6, R7, R8: 1K; R_Axial_DIN0207_L6.3mm_D2.5mm_P2.54mm_Vertical

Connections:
+12V: D1.1 (K), D2.1 (K), D3.1 (K), D4.1 (K), J1.2, J2.2, JP1.2, JP2.2, JP3.2, JP4.2, K1.3 (L1), K2.3 (L1), K3.3 (L1), K4.3 (L1), R1.2, R4.2, R6.2, R8.2
COM1: J4.2, K1.5 (COM1), K1.6 (COM2)
COM2: J5.2, K2.5 (COM1), K2.6 (COM2)
COM3: J6.2, K3.5 (COM1), K3.6 (COM2)
COM4: J7.2, K4.5 (COM1), K4.6 (COM2)
DRAIN1: D1.2 (A), J4.4, K1.4 (L2), Q1.3 (D)
DRAIN2: D2.2 (A), J5.4, K2.4 (L2), Q2.3 (D)
DRAIN3: D3.2 (A), J6.4, K3.4 (L2), Q3.3 (D)
DRAIN4: D4.2 (A), J7.4, K4.4 (L2), Q4.3 (D)
GND: J1.1, J2.1, Q1.1 (S), Q2.1 (S), Q3.1 (S), Q4.1 (S), R2.1, R3.1, R5.1, R7.1
NC1: J4.1, K1.2 (NC)
NC2: J5.1, K2.2 (NC)
NC3: J6.1, K3.2 (NC)
NC4: J7.1, K4.2 (NC)
NO1: J4.3, K1.1 (NO)
NO2: J5.3, K2.1 (NO)
NO3: J6.3, K3.1 (NO)
NO4: J7.3, K4.1 (NO)
unnamed: J4.5, JP1.1, R1.1
unnamed: J5.5, JP2.1, R4.1
unnamed: J6.5, JP3.1, R6.1
unnamed: J7.5, JP4.1, R8.1
SIG1: J3.1, Q1.2 (G), R2.2
SIG2: J3.2, Q2.2 (G), R3.2
SIG3: J3.3, Q3.2 (G), R5.2
SIG4: J3.4, Q4.2 (G), R7.2

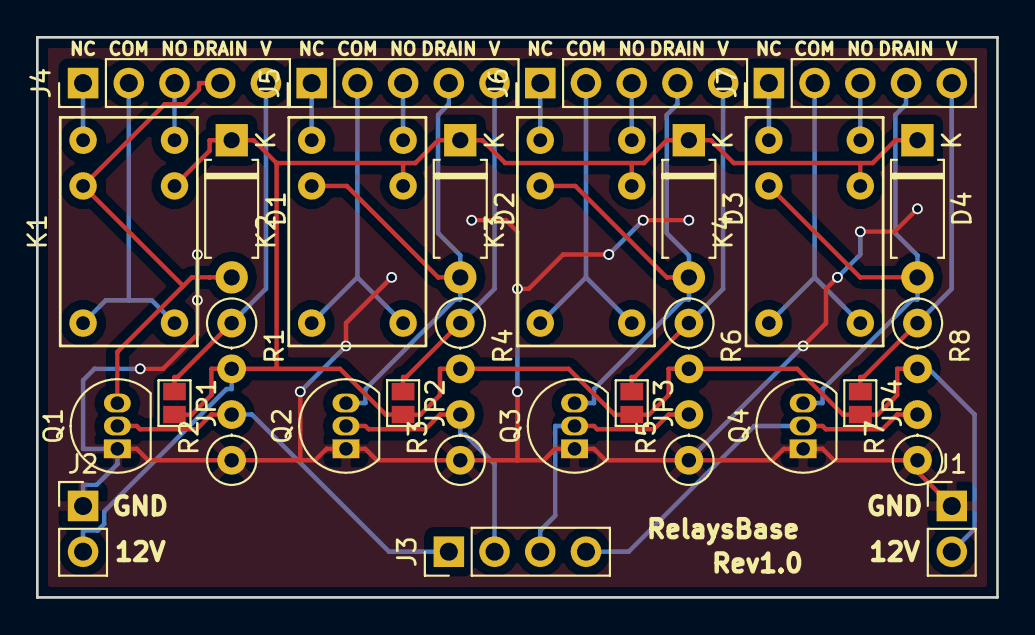
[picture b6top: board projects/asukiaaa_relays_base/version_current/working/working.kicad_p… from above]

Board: 2 copper layers, 53.3 x 31.1 mm, 31 parts (0 on the bottom side), 26 nets.

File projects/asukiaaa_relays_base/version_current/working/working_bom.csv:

"Id";"Designator";"Footprint";"Quantity";"Designation";"Supplier and ref";
1;"R8,R1,R2,R3,R4,R5,R6,R7";"R_Axial_DIN0207_L6.3mm_D2.5mm_P2.54mm_Vertical";8;"1K";;;
2;"J1,J2";"PinHeader_1x02_P2.54mm_Vertical";2;"Conn_01x02";;;
3;"J3";"PinHeader_1x04_P2.54mm_Vertical";1;"Conn_01x04";;;
4;"J4,J5,J6,J7";"PinHeader_1x05_P2.54mm_Vertical";4;"Conn_01x05";;;
5;"K1,K2,K3,K4";"Relay_Y14";4;"Y14";;;
6;"Q1,Q2,Q3,Q4";"TO-92_Inline";4;"Q_NMOS_SGD";;;
7;"D1,D2,D3,D4";"D_A-405_P7.62mm_Horizontal";4;"D";;;
